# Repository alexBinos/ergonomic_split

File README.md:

# ergonomic_split
An ergonomic split keyboard

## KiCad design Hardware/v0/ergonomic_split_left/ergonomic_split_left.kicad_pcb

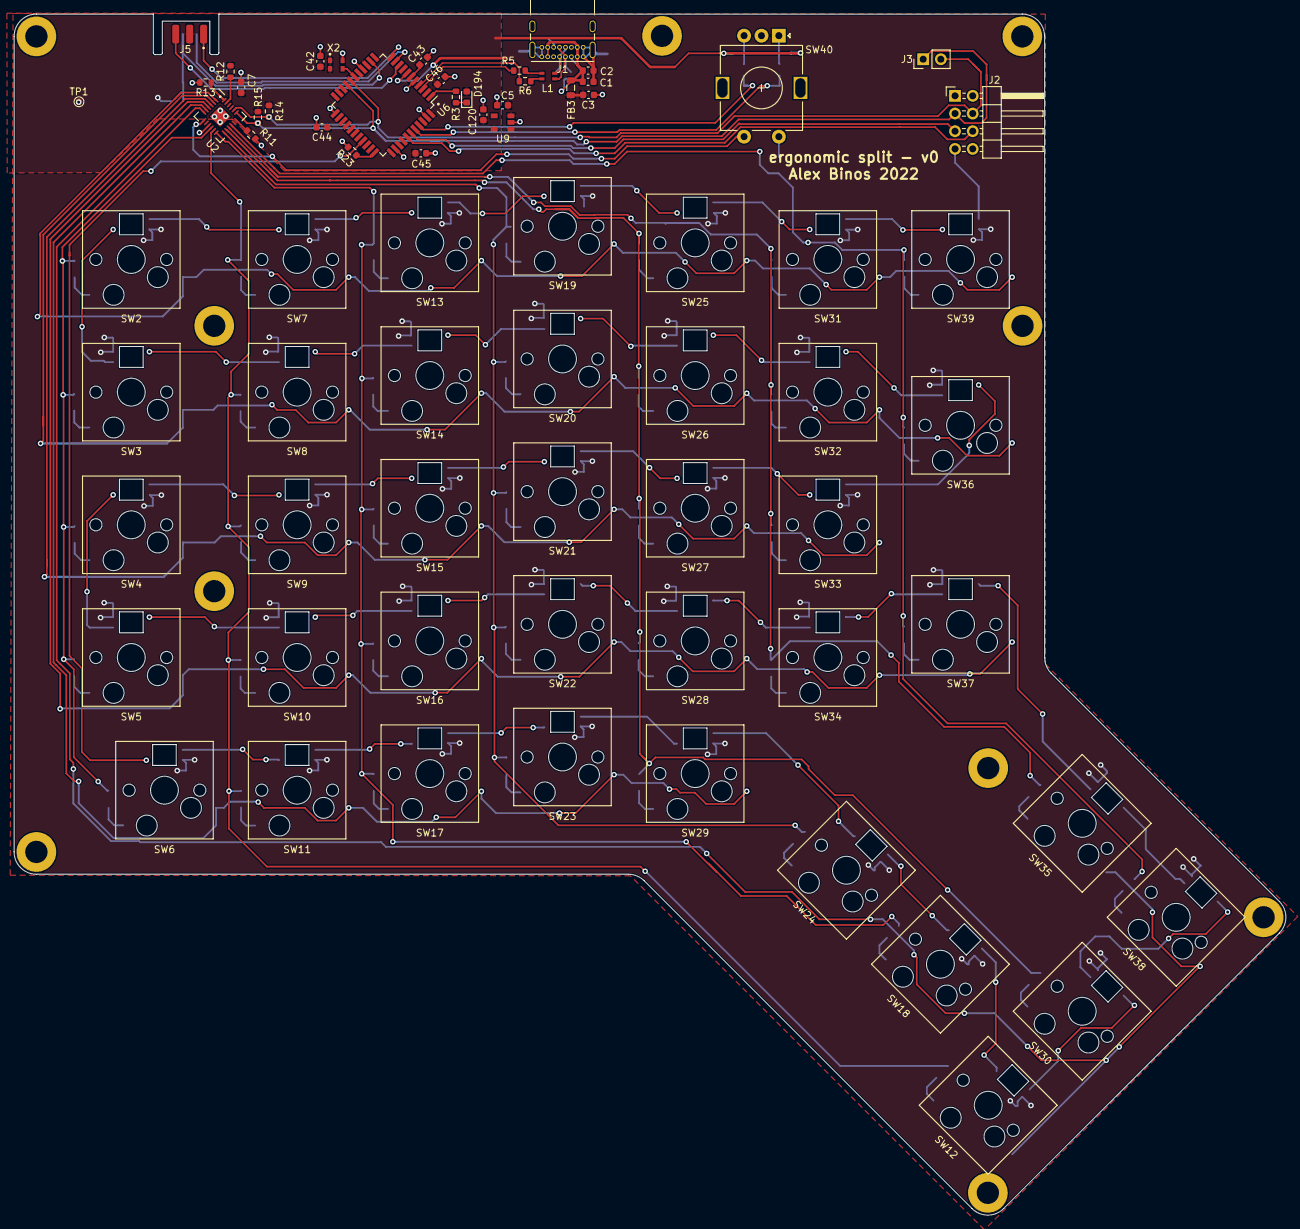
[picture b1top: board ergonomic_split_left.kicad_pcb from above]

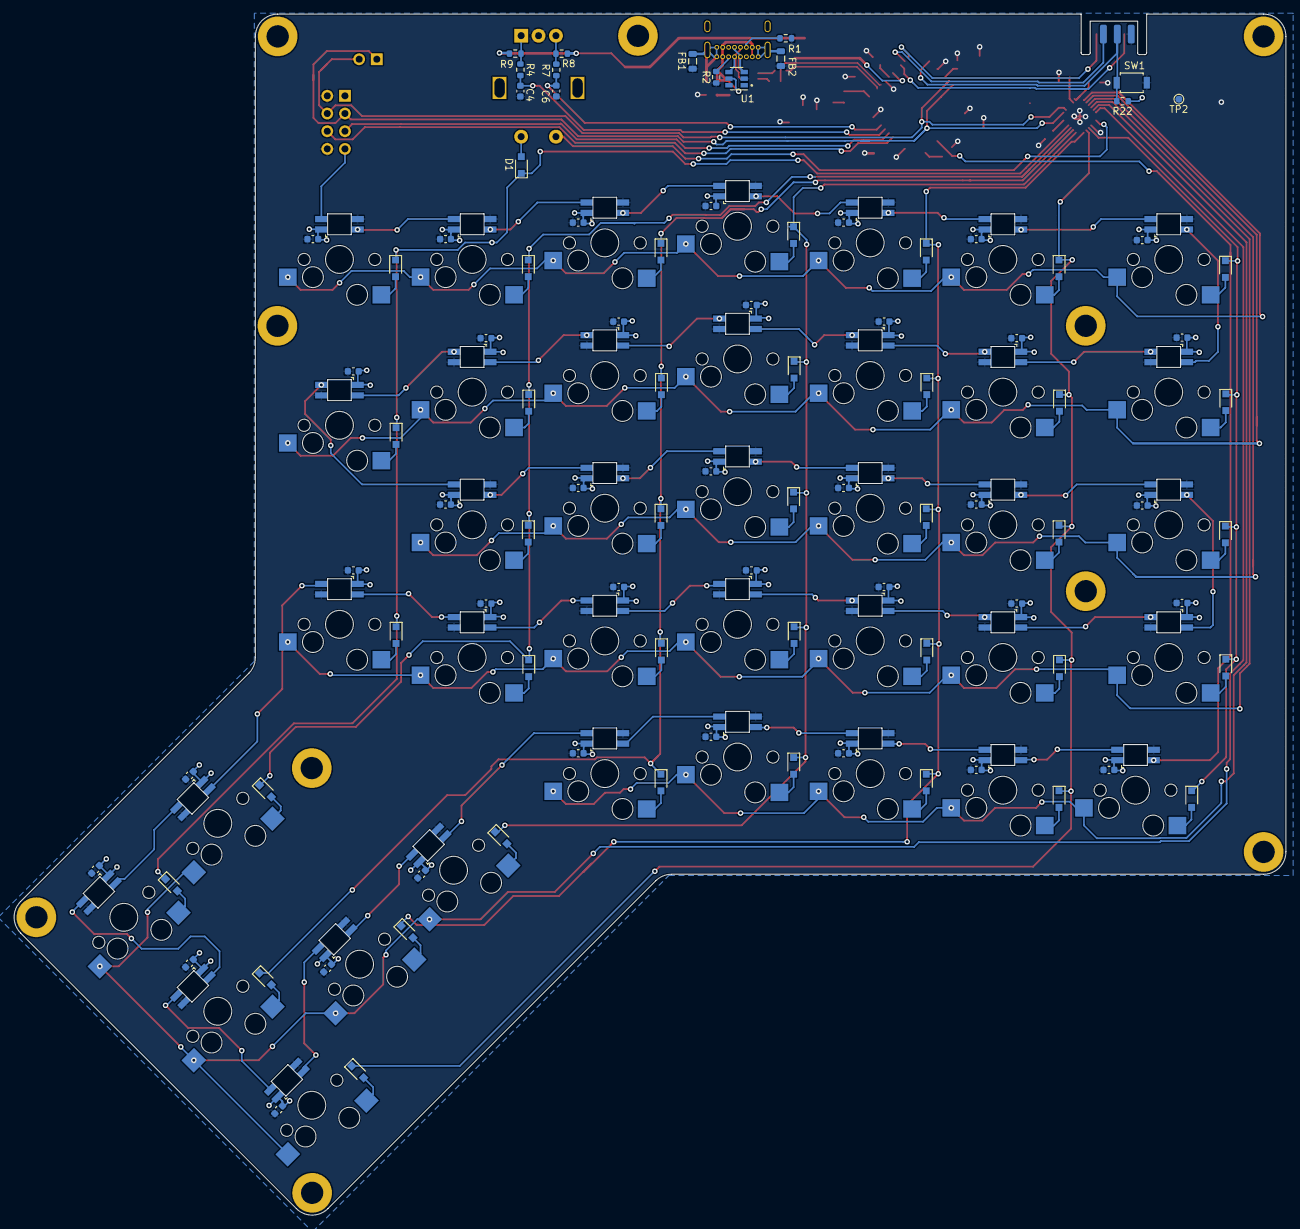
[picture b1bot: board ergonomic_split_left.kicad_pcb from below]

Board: 2 copper layers, 182.6 x 172.4 mm, 96 parts (15 on the bottom side), 125 nets.

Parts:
C1: 10uF; C_0603_1608Metric
C2, C43, C46, C120: 1uF; C_0603_1608Metric
C3, C4, C5, C6, C7, C42, C44, C45: 100nF; C_0603_1608Metric
D1: D; SOD323_HS
D194: LED; D_0603_1608Metric
FB1, FB2, FB3: Ferrite_Bead; L_0805_2012Metric
H1, H2, H3, H4, H5, H6, H7, H8, H9, H10: MountingHole_Pad; MountingHole_3.2mm_M3_ISO7380_Pad
J1: USB_C_Receptacle_USB2.0; USB_C_Receptacle_GCT_USB4085
J2: Right_Interface; PinHeader_2x04_P2.54mm_Horizontal
J3: Conn_01x02_Male; PinHeader_1x02_P2.54mm_Vertical
J5: Conn_02x03_Odd_Even; Conn_AVX_PCB_Edge_02x03
L1: L_Core_Iron_Coupled_1423; SMM2012E
R1, R2: 5K1; R_0603_1608Metric
R3: 330R; R_0603_1608Metric
R4, R7, R11, R12, R13, R22, R23: 10K; R_0603_1608Metric
R5, R6: 22R; R_0603_1608Metric
R8, R9: 1K; R_0603_1608Metric
R14, R15: 2K2; R_0603_1608Metric
SW1: SW_Push; SW_SPST_B3U-1000P
SW2: L00; CherryMX_1.50u_KailhSocket_Integrated_Reversed
SW3: L10; CherryMX_1.50u_KailhSocket_Integrated
SW4: L20; CherryMX_1.50u_KailhSocket_Integrated_Reversed
SW5: L30; CherryMX_1.50u_KailhSocket_Integrated
SW6: L40; CherryMX_1.00u_KailhSocket_Integrated_Reversed
SW7: L01; CherryMX_1.00u_KailhSocket_Integrated_Reversed
SW8: L11; CherryMX_1.00u_KailhSocket_Integrated
SW9: L21; CherryMX_1.00u_KailhSocket_Integrated_Reversed
SW10: L31; CherryMX_1.00u_KailhSocket_Integrated
SW11: L41; CherryMX_1.00u_KailhSocket_Integrated_Reversed
SW12: L51; CherryMX_1.00u_KailhSocket_Integrated_Reversed
SW13: L02; CherryMX_1.00u_KailhSocket_Integrated_Reversed
SW14: L12; CherryMX_1.00u_KailhSocket_Integrated
SW15: L22; CherryMX_1.00u_KailhSocket_Integrated_Reversed
SW16: L32; CherryMX_1.00u_KailhSocket_Integrated
SW17: L42; CherryMX_1.00u_KailhSocket_Integrated_Reversed
SW18: L52; CherryMX_2.00u_KailhSocket_Integrated_Vertical_Reversed
SW19: L03; CherryMX_1.00u_KailhSocket_Integrated_Reversed
SW20: L13; CherryMX_1.00u_KailhSocket_Integrated
SW21: L23; CherryMX_1.00u_KailhSocket_Integrated_Reversed
SW22: L33; CherryMX_1.00u_KailhSocket_Integrated
SW23: L43; CherryMX_1.00u_KailhSocket_Integrated_Reversed
SW24: L53; CherryMX_2.00u_KailhSocket_Integrated_Vertical_Reversed
SW25: L04; CherryMX_1.00u_KailhSocket_Integrated_Reversed
SW26: L14; CherryMX_1.00u_KailhSocket_Integrated
SW27: L24; CherryMX_1.00u_KailhSocket_Integrated_Reversed
SW28: L34; CherryMX_1.00u_KailhSocket_Integrated
SW29: L44; CherryMX_1.00u_KailhSocket_Integrated_Reversed
SW30: L54; CherryMX_1.00u_KailhSocket_Integrated
SW31: L05; CherryMX_1.00u_KailhSocket_Integrated_Reversed
SW32: L15; CherryMX_1.00u_KailhSocket_Integrated
SW33: L25; CherryMX_1.00u_KailhSocket_Integrated_Reversed
SW34: L35; CherryMX_1.00u_KailhSocket_Integrated
SW35: L55; CherryMX_1.00u_KailhSocket_Integrated
SW36: L16; CherryMX_1.50u_KailhSocket_Integrated_Vertical
SW37: L36; CherryMX_1.50u_KailhSocket_Integrated_Vertical
SW38: L56; CherryMX_1.00u_KailhSocket_Integrated
SW39: L06; CherryMX_1.00u_KailhSocket_Integrated_Reversed
SW40: L_Encoder; RotaryEncoder_Alps_EC11E-Switch_Vertical_H20mm
TP1, TP2: TestPoint; TestPoint_Pad_D1.0mm
U1: SRV05-4; SOT-23-6
U2: PCAL9555AHF; QFN-24_EP_5x5_Pitch0.5mm
U6: ATmega32U4-AU; TQFP-44_10x10mm_P0.8mm
U9: TCR2EF33; TCR2EF33_SOT25
X2: KC2016K

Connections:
+3V3: C7.1, C42.1, C44.1, C45.1, C46.1, C120.1, D194.2, J5.2, R8.2, R9.2, R12.2, R14.1, R15.1, R22.1, U2.21, U6.2, U6.14, U6.24, U6.34, U6.42, U6.44, U9.5, X2.1, X2.4
+5V: C3.1, C5.1, FB3.1, J2.1, SW2.5, SW2.9, SW3.5, SW3.9, SW4.5, SW4.9, SW5.5, SW5.9, SW6.5, SW6.9, SW7.5, SW7.9, SW8.5, SW8.9, SW9.5, SW9.9, SW10.5, SW10.9, SW11.5, SW11.9, SW12.5, SW12.9, SW13.5, SW13.9, SW14.5, SW14.9, SW15.5, SW15.9, SW16.5, SW16.9, SW17.5, SW17.9, SW18.5, SW18.9, SW19.5, SW19.9, SW20.5, SW20.9, SW21.5, SW21.9, SW22.5, SW22.9, SW23.5, SW23.9, SW24.5, SW24.9, SW25.5, SW25.9, SW26.5, SW26.9, SW27.5, SW27.9, SW28.5, SW28.9, SW29.5, SW29.9, SW30.5, SW30.9, SW31.5, SW31.9, SW32.5, SW32.9, SW33.5, SW33.9, SW34.5, SW34.9, SW35.5, SW35.9, SW36.5, SW36.9, SW37.5, SW37.9, SW38.5, SW38.9, SW39.5, SW39.9, U6.7, U9.1, U9.3
/IO Expander/COL[0]: SW2.4, SW3.4, SW4.4, SW5.4, SW6.4, U2.10
/IO Expander/COL[1]: SW7.4, SW8.4, SW9.4, SW10.4, SW11.4, SW12.4, U2.11
/IO Expander/COL[2]: SW13.4, SW14.4, SW15.4, SW16.4, SW17.4, SW18.4, U2.12
/IO Expander/COL[3]: SW19.4, SW20.4, SW21.4, SW22.4, SW23.4, SW24.4, U2.13
/IO Expander/COL[4]: SW25.4, SW26.4, SW27.4, SW28.4, SW29.4, SW30.4, U2.14
/IO Expander/COL[5]: SW31.4, SW32.4, SW33.4, SW34.4, SW35.4, U2.15
/IO Expander/COL[6]: D1.1, SW36.4, SW37.4, SW38.4, SW39.4, U2.16
/IO Expander/ROW[0]: SW2.1, SW7.1, SW13.1, SW19.1, SW25.1, SW31.1, SW39.1, U2.1
/IO Expander/ROW[1]: SW3.1, SW8.1, SW14.1, SW20.1, SW26.1, SW32.1, SW36.1, U2.2
/IO Expander/ROW[2]: SW4.1, SW9.1, SW15.1, SW21.1, SW27.1, SW33.1, U2.3
/IO Expander/ROW[3]: SW5.1, SW10.1, SW16.1, SW22.1, SW28.1, SW34.1, SW37.1, U2.4
/IO Expander/ROW[4]: SW6.1, SW11.1, SW17.1, SW23.1, SW29.1, U2.5
/IO Expander/ROW[5]: SW12.1, SW18.1, SW24.1, SW30.1, SW35.1, SW38.1, U2.6
/IO Expander/ROW[6]: SW40.S1, U2.7
/IO Expander/SCL: J2.4, J3.2, R14.2, U2.20, U6.18
/IO Expander/SDA: J2.3, J3.1, R15.2, U2.19, U6.19
/Right Interface/ENCODER_A_R: J2.5, U6.39
/Right Interface/ENCODER_B_R: J2.6, U6.38
/Right Interface/RGB_DIN: J2.7, SW39.6
/Switch Matrix/ENCODER_A_L: C4.1, R4.2, U6.40
/Switch Matrix/ENCODER_B_L: C6.1, R7.2, U6.41
/Switch Matrix/RGB_DIN: SW6.8, U6.30
/Switch Matrix/RGB_L44: SW24.8, SW29.6
/Switch Matrix/RGB_L51: SW12.6, SW30.8
/Switch Matrix/RGB_L54: SW30.6, SW38.8
/Switch Matrix/RGB_L55: SW35.6, SW37.8
/USB_UPSTREAM/CD+: J1.A6, J1.B6, L1.3, U1.4
/USB_UPSTREAM/CD-: J1.A7, J1.B7, L1.4, U1.3
/USB_UPSTREAM/D+: L1.2, R6.2
/USB_UPSTREAM/D-: L1.1, R5.2
/USB_UPSTREAM/USB+: R6.1, U6.4
/USB_UPSTREAM/USB-: R5.1, U6.3
/uController/MISO: J5.1, U6.11
/uController/MOSI: J5.4, U6.10
/uController/RST: J5.5, R22.2, SW1.1, U6.13
/uController/SCK: J5.3, U6.9
/uController/nCAPS_LED: R3.1, U6.1
GND: C3.2, C4.2, C5.2, C6.2, C7.2, C42.2, C43.2, C44.2, C45.2, C46.2, C120.2, FB1.1, FB2.1, J2.2, J2.8, J5.6, R1.1, R2.1, R11.2, R13.2, R23.2, SW1.2, SW2.7, SW2.10, SW3.7, SW3.10, SW4.7, SW4.10, SW5.7, SW5.10, SW6.7, SW6.10, SW7.7, SW7.10, SW8.7, SW8.10, SW9.7, SW9.10, SW10.7, SW10.10, SW11.7, SW11.10, SW12.7, SW12.10, SW13.7, SW13.10, SW14.7, SW14.10, SW15.7, SW15.10, SW16.7, SW16.10, SW17.7, SW17.10, SW18.7, SW18.10, SW19.7, SW19.10, SW20.7, SW20.10, SW21.7, SW21.10, SW22.7, SW22.10, SW23.7, SW23.10, SW24.7, SW24.10, SW25.7, SW25.10, SW26.7, SW26.10, SW27.7, SW27.10, SW28.7, SW28.10, SW29.7, SW29.10, SW30.7, SW30.10, SW31.7, SW31.10, SW32.7, SW32.10, SW33.7, SW33.10, SW34.7, SW34.10, SW35.7, SW35.10, SW36.7, SW36.10, SW37.7, SW37.10, SW38.7, SW38.10, SW39.7, SW39.10, SW40.C, TP1.1, TP2.1, U1.2, U2.9, U2.25, U6.5, U6.15, U6.23, U6.35, U6.43, U9.2, X2.2
unnamed: C1.2, C2.2, FB1.2, FB2.2, J1.A1, J1.A12, J1.B1, J1.B12, J1.S1
unnamed: C43.1, U6.6
unnamed: D1.2, SW40.S2
unnamed: D194.1, R3.2
unnamed: J1.A5, R2.2
unnamed: J1.B5, R1.2
unnamed: R4.1, R9.1, SW40.A
unnamed: R7.1, R8.1, SW40.B
unnamed: R11.1, U2.18
unnamed: R12.1, U2.23
unnamed: R13.1, U2.24
unnamed: R23.1, U6.33
unnamed: SW2.2, SW2.3
unnamed: SW2.6, SW7.8
unnamed: SW2.8, SW3.6
unnamed: SW3.2, SW3.3
unnamed: SW3.8, SW8.6
unnamed: SW4.2, SW4.3
unnamed: SW4.6, SW9.8
unnamed: SW4.8, SW5.6
unnamed: SW5.2, SW5.3
unnamed: SW6.2, SW6.3
unnamed: SW7.2, SW7.3
unnamed: SW8.2, SW8.3
unnamed: SW9.2, SW9.3
unnamed: SW10.2, SW10.3
unnamed: SW5.8, SW10.6
unnamed: SW10.8, SW16.6
unnamed: SW11.2, SW11.3
unnamed: SW11.6, SW17.8
unnamed: SW6.6, SW11.8
unnamed: SW12.2, SW12.3
unnamed: SW12.8, SW18.6
unnamed: SW13.2, SW13.3
unnamed: SW13.6, SW19.8
unnamed: SW7.6, SW13.8
unnamed: SW14.2, SW14.3
unnamed: SW8.8, SW14.6
unnamed: SW14.8, SW20.6
unnamed: SW15.2, SW15.3
unnamed: SW15.6, SW21.8
unnamed: SW9.6, SW15.8
unnamed: SW16.2, SW16.3
unnamed: SW16.8, SW22.6
unnamed: SW17.2, SW17.3
unnamed: SW17.6, SW23.8
unnamed: SW18.2, SW18.3
unnamed: SW18.8, SW24.6
unnamed: SW19.2, SW19.3
unnamed: SW19.6, SW25.8
unnamed: SW20.2, SW20.3
unnamed: SW20.8, SW26.6
unnamed: SW21.2, SW21.3
unnamed: SW21.6, SW27.8
unnamed: SW22.2, SW22.3
unnamed: SW22.8, SW28.6
unnamed: SW23.2, SW23.3
unnamed: SW23.6, SW29.8
unnamed: SW24.2, SW24.3
unnamed: SW25.2, SW25.3
unnamed: SW25.6, SW31.8
unnamed: SW26.2, SW26.3
unnamed: SW26.8, SW32.6
unnamed: SW27.2, SW27.3
unnamed: SW27.6, SW33.8
unnamed: SW28.2, SW28.3
unnamed: SW28.8, SW34.6
unnamed: SW29.2, SW29.3
unnamed: SW30.2, SW30.3
unnamed: SW31.2, SW31.3
unnamed: SW31.6, SW39.8
unnamed: SW32.2, SW32.3
unnamed: SW32.8, SW36.6
unnamed: SW33.2, SW33.3
unnamed: SW33.6, SW36.8
unnamed: SW34.2, SW34.3
unnamed: SW34.8, SW37.6
unnamed: SW35.2, SW35.3
unnamed: SW35.8, SW38.6
unnamed: SW36.2, SW36.3
unnamed: SW37.2, SW37.3
unnamed: SW38.2, SW38.3
unnamed: SW39.2, SW39.3
unnamed: U6.17, X2.3
VBUS: C1.1, C2.1, FB3.2, J1.A4, J1.A9, J1.B4, J1.B9, U1.5

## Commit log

2022-06-04 Updating gitignore
2022-06-04 Creating KiCAD project, starting schematic design
2022-06-04 Adding .lib
2022-06-04 Switch matrix placement
2022-06-04 Connecting schematic blocks, most sub-blocks done
2022-06-04 Drawing board outline Basic placement done Adding rotary encoder to the switch matrix Adding mounting holes
2022-06-05 Adding power and ground planes Adding right interface USB C connector Pin swapping on ATMEGA
2022-06-05 Debug connectors Adding I2C debug header Changed SPI programming header to edge mount Changed right interface connector to IDC Cleaning up schematic
2022-06-05 Switch matrix and LEDs prelim routing
2022-06-05 Prelim routing done
2022-06-06 Moving board edges in to 0.1in from keyswitches
2022-06-06 Fixing power planes and connector positions
2022-06-06 Cleaning up routing
2022-06-06 Passes DRC Fixed component clashes Fixed traces blocking 5V0 power plane
2022-06-07 Creating blank KiCAD project for right side PCB
2022-06-07 High level schematic done
2022-06-08 Board outline, power planes and component placement
2022-06-08 Moving right interface connector
2022-06-11 Right side prelim routing mostly done
2022-06-11 Cleaning routing, fixing 3V3 plane
2022-06-11 Adding input caps on 5V0
2022-06-11 Cleaning up silk
2022-06-13 Adding firmware with default keymap
2022-07-02 Starting firmware from compilable state
2022-07-03 Creating Arduino Uno project to test PCAL9555 functions
2022-07-04 Implemented register writes
2022-07-04 Implemented write back
2022-07-06 Cutting down redundant code, scanning algorithm working
2022-07-09 Fixing board edge around edge connector causing STEP to not generate correctly. Adding 3D model for USB C connector
2022-07-09 Updating component 3d models
2022-07-09 Adding gerbers
2022-07-09 Tidying last few traces
2022-07-09 Schematic title page
2022-07-09 V0 schematic PDFs
2022-07-19 Implemented scanning algorithm for master side
2022-07-24 Fixing right interface connector 3D model
2022-07-25 Scanning algorithm working, adding RGB and caps leds
2022-07-26 Drawing around reset switch for mechanical
2022-07-26 Adding left side DXFs
2022-07-26 Front courtyard DXF
2022-07-26 First pass of case
2022-08-06 Fixing USB connector and stand nut clearances
2022-08-06 Adding keyframe and stand STLs
2022-08-07 Right side mechanicals
2022-08-09 ICSP 6 pin debug header to edge connector adapter board
2022-08-09 Right side DXFs
2022-08-09 Issues record
2022-08-10 Adding debug counter readout
2022-08-10 Fixing stand cutouts
2022-08-13 Fixing caps LED and reset cutouts
2022-08-20 Right side scanning working
2022-08-22 Changing thickness to 1.2mm, minor fixes
2022-08-30 Scanning algorithm working
2022-09-03 Adding a temporary work around
2022-09-11 Adding i2c fix image
2022-09-23 Starting firmware from scratch
2022-09-24 Default keymap
2022-09-24 Fixing keymap errors, adding config file
2022-09-25 Keymap compiles, formatting
2022-10-08 Implementing matrix scanning algorithm
2022-10-08 Long keypress working
2022-10-15 Adding lighting control to keymap
2022-10-16 Updating keymap, working on layer 2
2022-10-16 Fixing right side keyframe width
2022-10-24 Adding left encoder
